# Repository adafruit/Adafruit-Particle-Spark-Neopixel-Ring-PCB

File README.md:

## Adafruit Particle Spark Neopixel Ring PCB
<a href="http://www.adafruit.com/products/2268"><br/>
Click here to purchase one from the Adafruit shop</a>

Add some dazzle to your Spark Core or Photon with this custom-made NeoPixel ring kit! 24 ultra bright smart LED NeoPixels are arranged in a circle with 2.6" (66mm) outer diameter. Snap in your Spark and upload the NeoPixel library code to light up the LEDs, make an Internet of Blinky! Each LED is addressable as the driver chip is inside the LED. Each one has ~18mA constant current drive so the color will be very consistent even if the voltage varies, and no external choke resistors are required making the design slim. Power the whole thing with about 3.5-5.5 VDC battery pack and you're ready to rock.

To make your project portable, we have a JST connector for attaching an external battery. Power with 3.5 - 5.5V DC, a rechargeable LiPoly or LiIon cell battery works great, or 3xAAA or 3xAA battery pack. The JST included is so you can make your own battery connection. Use pin D6 for the NeoPixel library code, all other pins are availale to use and have two breakouts on either side so you can wire up other sensors or devices.

Comes as a single round PCB with 24 individually addressable RGB LEDs assembled and tested, two 12 pin 0.1" socket headers and a bonus JST cable. Some light soldering is required, you can solder the two sockets in place to allow unplugging of the Spark, or just solder it directly in place for a slimmer look.

PCB files for the Adafruit Particle/Spark Neopixel Ring
- https://www.adafruit.com/product/2268

### License

Adafruit invests time and resources providing this open source design, please support Adafruit and open-source hardware by purchasing products from [Adafruit](https://www.adafruit.com)!

All text above must be included in any redistribution

Designed by Limor Fried/Ladyada for Adafruit Industries.
Creative Commons Attribution/Share-Alike, all text above must be included in any redistribution. 
See license.txt for additional information.

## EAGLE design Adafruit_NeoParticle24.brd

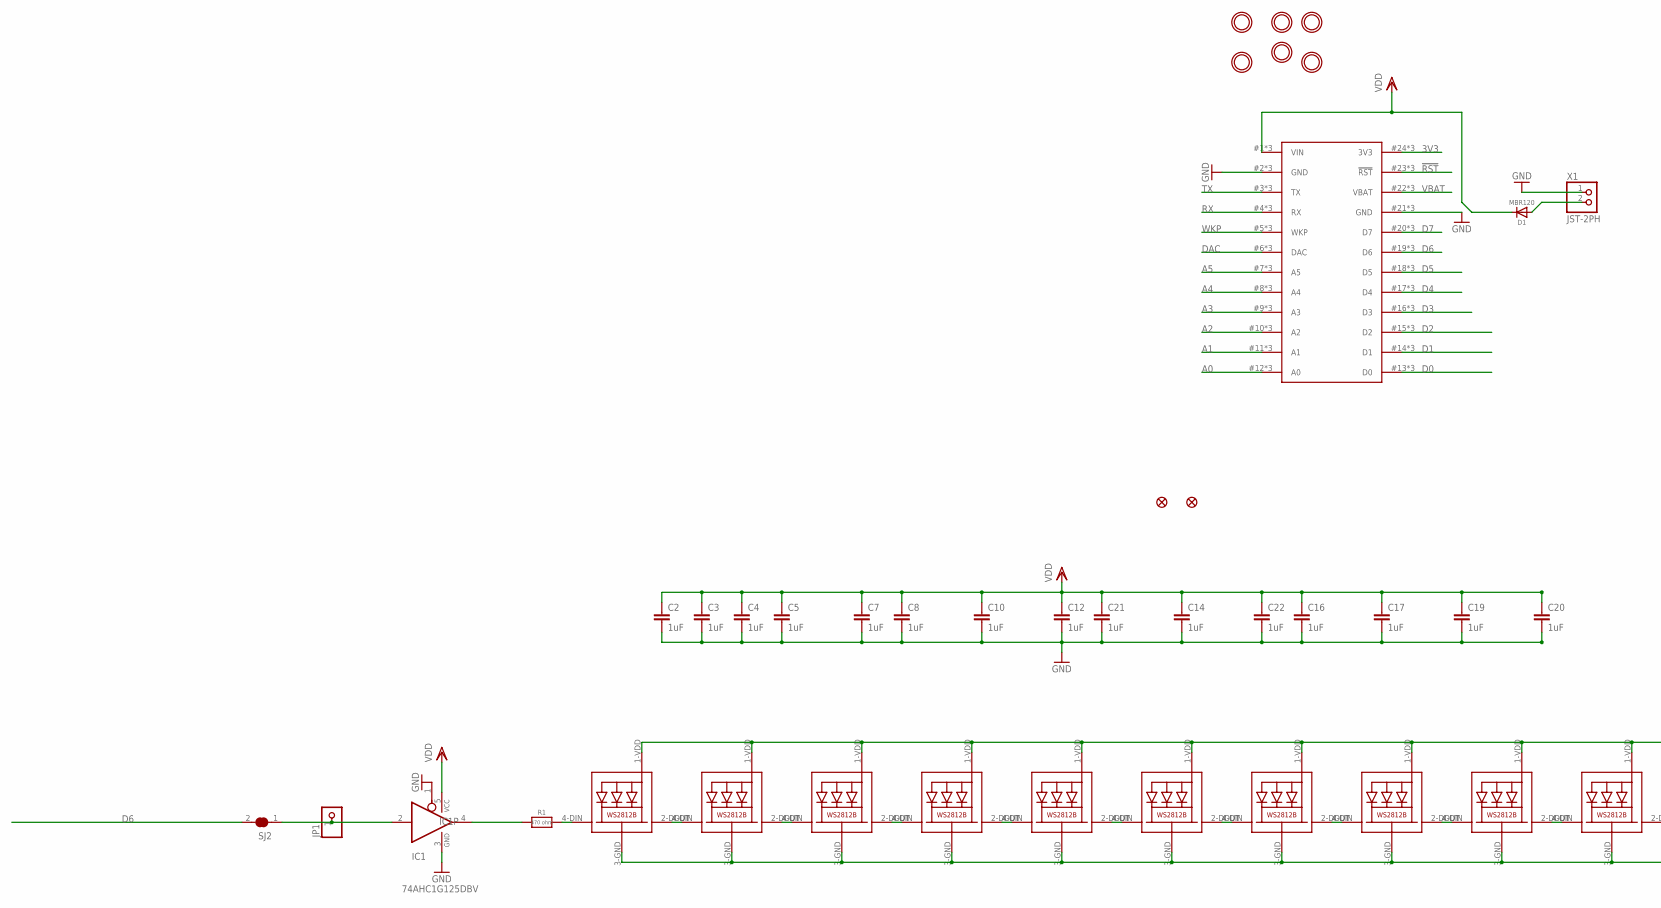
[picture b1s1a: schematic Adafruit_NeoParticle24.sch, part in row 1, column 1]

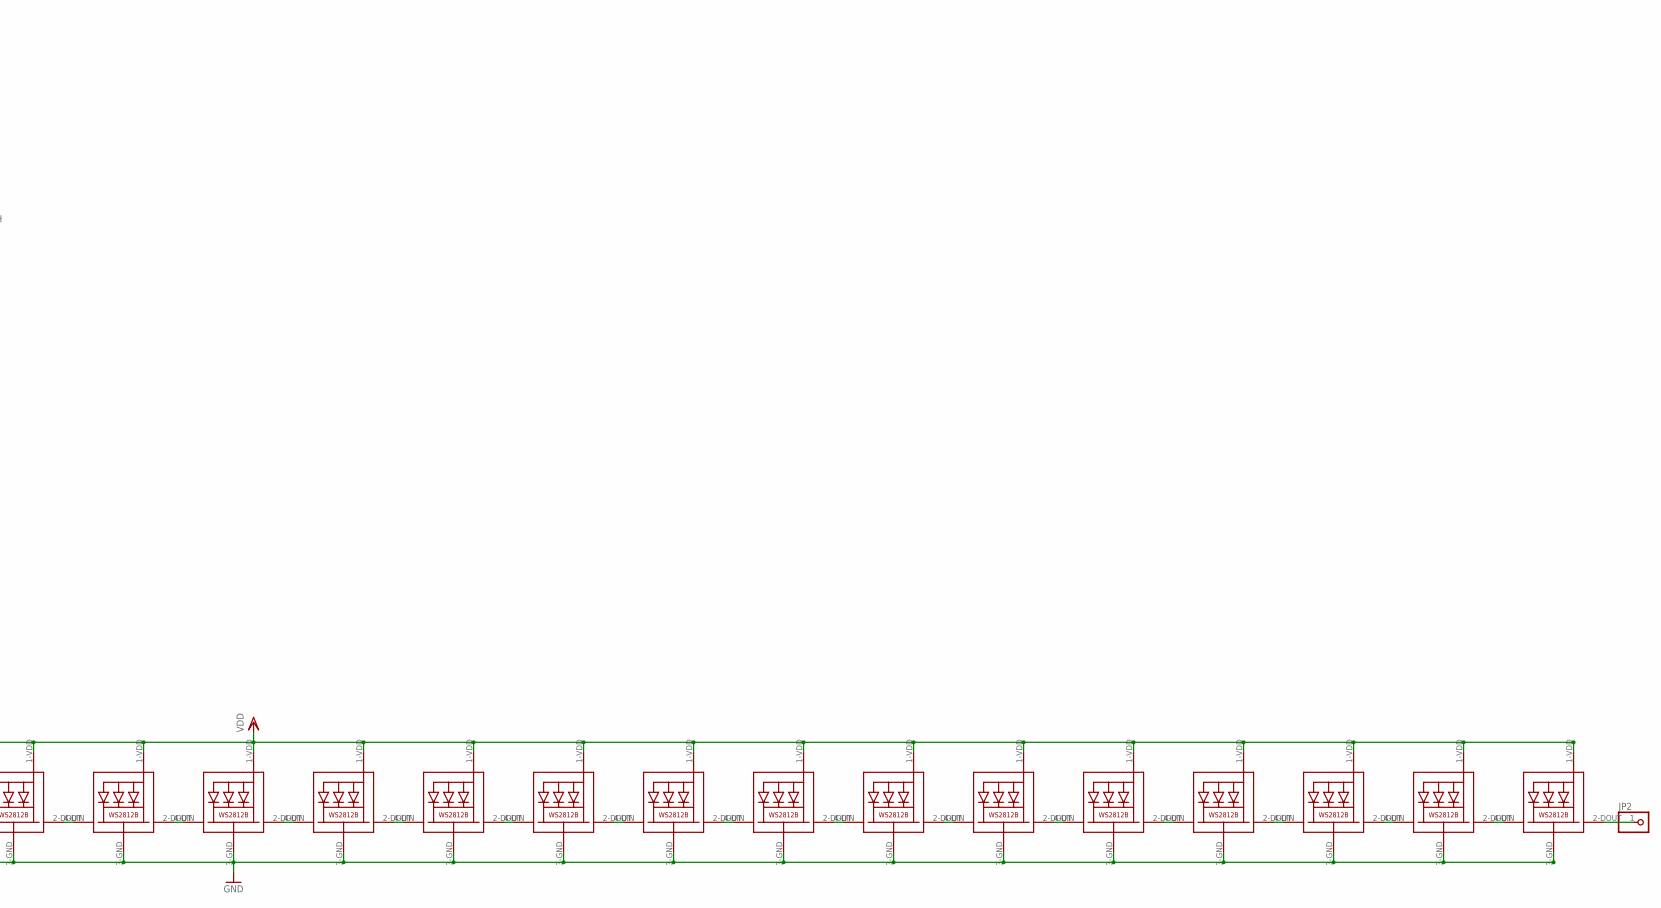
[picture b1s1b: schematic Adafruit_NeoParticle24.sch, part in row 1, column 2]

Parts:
C2, C3, C4, C5, C7, C8, C10, C12, C14, C16, C17, C19, C20, C21, C22: 1uF; C0603
D1: MBR120; SOD-123
FID1, FID2: FIDUCIAL""; FIDUCIAL_1MM
IC1: 74AHC1G125DBV; SOT23-5
JP1: HEADER-1X1ROUND; 1X01_ROUND
JP2: PINHD-1X1CB; 1X01-CLEANBIG
LED1, LED2, LED3, LED4, LED5, LED6, LED7, LED8, LED9, LED10, LED11, LED12, LED13, LED14, LED15, LED16, LED17, LED18, LED19, LED20, LED21, LED22, LED23, LED24: WS2812B5050; WS2812B-NARROW
R1: 470 ohm; 0603-NO
SJ2: SOLDERJUMPER_CLOSED; SOLDERJUMPER_CLOSEDWIRE
U$2: PHOTON; SPARK_CORE_STACKABLE
U$3, U$4, U$5, U$6, U$9, U$10: MOUNTINGHOLE3.0THIN; MOUNTINGHOLE_3.0_PLATEDTHIN
X1: JST-2PH; JSTPH2

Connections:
3V3: U$2.24 (3V3), U$2.#24 (3V3), U$2.@24 (3V3)
!RST: U$2.23 (!RST), U$2.#23 (!RST), U$2.@23 (!RST)
A0: U$2.12 (A0), U$2.#12 (A0), U$2.@12 (A0)
A1: U$2.11 (A1), U$2.#11 (A1), U$2.@11 (A1)
A2: U$2.10 (A2), U$2.#10 (A2), U$2.@10 (A2)
A3: U$2.9 (A3), U$2.#9 (A3), U$2.@9 (A3)
A4: U$2.8 (A4), U$2.#8 (A4), U$2.@8 (A4)
A5: U$2.7 (A5), U$2.#7 (A5), U$2.@7 (A5)
D0: U$2.13 (D0), U$2.#13 (D0), U$2.@13 (D0)
D1: U$2.14 (D1), U$2.#14 (D1), U$2.@14 (D1)
D2: U$2.15 (D2), U$2.#15 (D2), U$2.@15 (D2)
D3: U$2.16 (D3), U$2.#16 (D3), U$2.@16 (D3)
D4: U$2.17 (D4), U$2.#17 (D4), U$2.@17 (D4)
D5: U$2.18 (D5), U$2.#18 (D5), U$2.@18 (D5)
D6: SJ2.2, U$2.19 (D6), U$2.#19 (D6), U$2.@19 (D6)
D7: U$2.20 (D7), U$2.#20 (D7), U$2.@20 (D7)
DAC: U$2.6 (DAC), U$2.#6 (DAC), U$2.@6 (DAC)
DIN: IC1.2 (I), JP1.1, SJ2.1
GND: C2.2, C3.2, C4.2, C5.2, C7.2, C8.2, C10.2, C12.2, C14.2, C16.2, C17.2, C19.2, C20.2, C21.2, C22.2, IC1.1 (OE), IC1.3 (GND), LED1.3-GND (GND), LED2.3-GND (GND), LED3.3-GND (GND), LED4.3-GND (GND), LED5.3-GND (GND), LED6.3-GND (GND), LED7.3-GND (GND), LED8.3-GND (GND), LED9.3-GND (GND), LED10.3-GND (GND), LED11.3-GND (GND), LED12.3-GND (GND), LED13.3-GND (GND), LED14.3-GND (GND), LED15.3-GND (GND), LED16.3-GND (GND), LED17.3-GND (GND), LED18.3-GND (GND), LED19.3-GND (GND), LED20.3-GND (GND), LED21.3-GND (GND), LED22.3-GND (GND), LED23.3-GND (GND), LED24.3-GND (GND), U$2.2 (GND), U$2.21 (GND), U$2.#2 (GND), U$2.#21 (GND), U$2.@2 (GND), U$2.@21 (GND), X1.1
unnamed: LED1.2-DOUT (DO), LED2.4-DIN (DI)
unnamed: LED2.2-DOUT (DO), LED3.4-DIN (DI)
unnamed: LED3.2-DOUT (DO), LED4.4-DIN (DI)
unnamed: LED4.2-DOUT (DO), LED5.4-DIN (DI)
unnamed: LED5.2-DOUT (DO), LED6.4-DIN (DI)
unnamed: LED6.2-DOUT (DO), LED7.4-DIN (DI)
unnamed: LED7.2-DOUT (DO), LED8.4-DIN (DI)
unnamed: LED8.2-DOUT (DO), LED9.4-DIN (DI)
unnamed: LED9.2-DOUT (DO), LED10.4-DIN (DI)
unnamed: LED10.2-DOUT (DO), LED11.4-DIN (DI)
unnamed: LED11.2-DOUT (DO), LED12.4-DIN (DI)
unnamed: LED12.2-DOUT (DO), LED13.4-DIN (DI)
unnamed: LED13.2-DOUT (DO), LED14.4-DIN (DI)
unnamed: LED14.2-DOUT (DO), LED15.4-DIN (DI)
unnamed: LED15.2-DOUT (DO), LED16.4-DIN (DI)
unnamed: LED16.2-DOUT (DO), LED17.4-DIN (DI)
unnamed: LED17.2-DOUT (DO), LED18.4-DIN (DI)
unnamed: LED18.2-DOUT (DO), LED19.4-DIN (DI)
unnamed: LED19.2-DOUT (DO), LED20.4-DIN (DI)
unnamed: LED20.2-DOUT (DO), LED21.4-DIN (DI)
unnamed: LED21.2-DOUT (DO), LED22.4-DIN (DI)
unnamed: LED22.2-DOUT (DO), LED23.4-DIN (DI)
unnamed: LED23.2-DOUT (DO), LED24.4-DIN (DI)
unnamed: JP2.1, LED24.2-DOUT (DO)
unnamed: LED1.4-DIN (DI), R1.2
unnamed: IC1.4 (O), R1.1
unnamed: D1.A, X1.2
RX: U$2.4 (RX), U$2.#4 (RX), U$2.@4 (RX)
TX: U$2.3 (TX), U$2.#3 (TX), U$2.@3 (TX)
VBAT: U$2.22 (VBAT), U$2.#22 (VBAT), U$2.@22 (VBAT)
VDD: C2.1, C3.1, C4.1, C5.1, C7.1, C8.1, C10.1, C12.1, C14.1, C16.1, C17.1, C19.1, C20.1, C21.1, C22.1, D1.C, IC1.5 (VCC), LED1.1-VDD (VDD), LED2.1-VDD (VDD), LED3.1-VDD (VDD), LED4.1-VDD (VDD), LED5.1-VDD (VDD), LED6.1-VDD (VDD), LED7.1-VDD (VDD), LED8.1-VDD (VDD), LED9.1-VDD (VDD), LED10.1-VDD (VDD), LED11.1-VDD (VDD), LED12.1-VDD (VDD), LED13.1-VDD (VDD), LED14.1-VDD (VDD), LED15.1-VDD (VDD), LED16.1-VDD (VDD), LED17.1-VDD (VDD), LED18.1-VDD (VDD), LED19.1-VDD (VDD), LED20.1-VDD (VDD), LED21.1-VDD (VDD), LED22.1-VDD (VDD), LED23.1-VDD (VDD), LED24.1-VDD (VDD), U$2.1 (VIN), U$2.#1 (VIN), U$2.@1 (VIN)
WKP: U$2.5 (WKP), U$2.#5 (WKP), U$2.@5 (WKP)

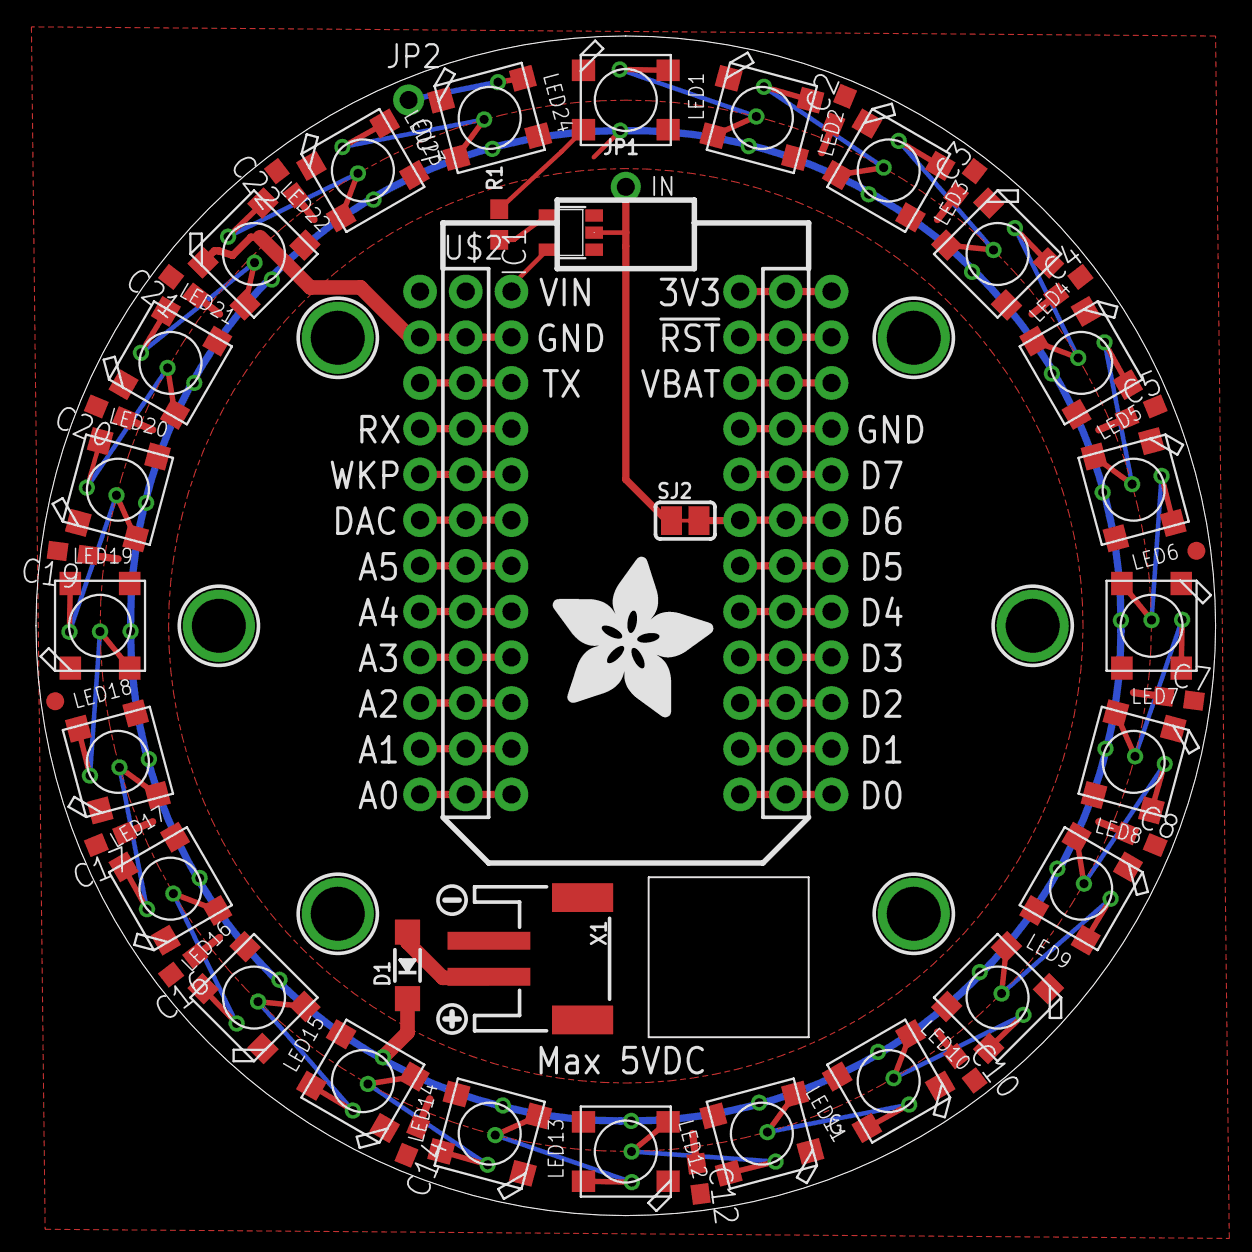
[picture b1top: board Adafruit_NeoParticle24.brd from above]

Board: 2 copper layers, 65.4 x 65.4 mm, 59 parts (1 on the bottom side), 51 nets.

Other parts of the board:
U$1: ADAFRUIT_9MM
U$7: SYMBOL_PLUS
U$8: SYMBOL_MINUS
U$11: PCBFEAT-REV-040

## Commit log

2015-09-02 init

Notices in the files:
parts and their libraries:
microbuilder: This work is placed in the public domain, and may be freely used for commercial and non-commercial work with the following conditions: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
